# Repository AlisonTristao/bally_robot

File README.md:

# 🤖 Bally Robot

Projeto do robô seguidor de linha bally

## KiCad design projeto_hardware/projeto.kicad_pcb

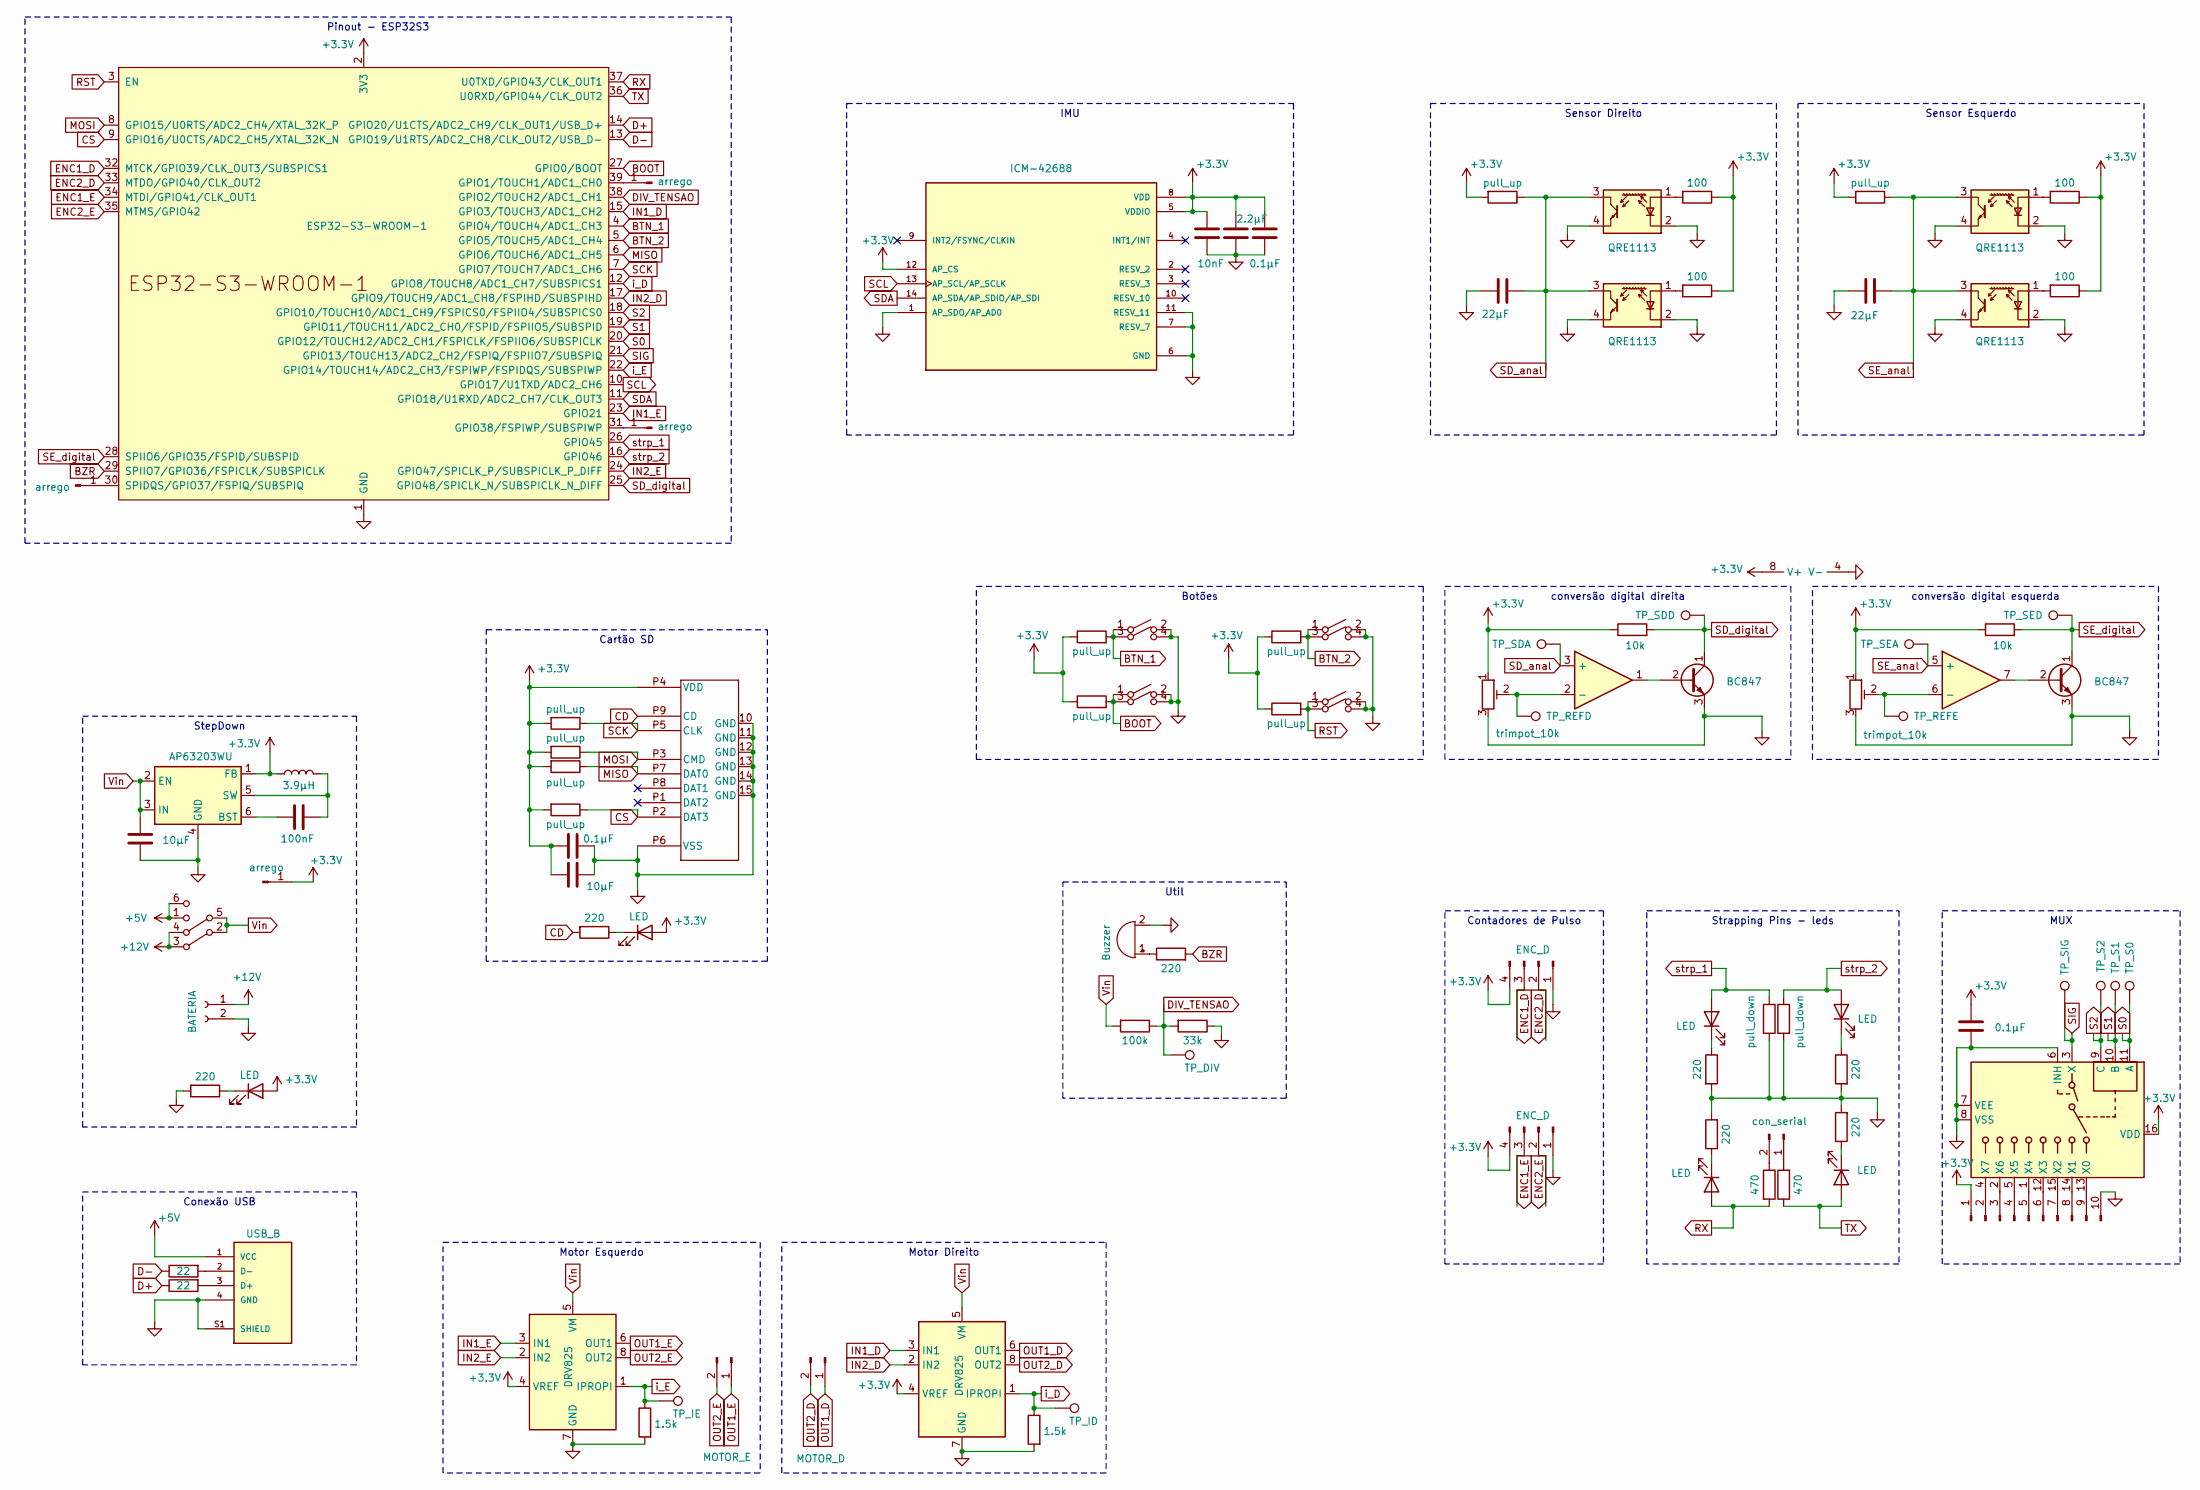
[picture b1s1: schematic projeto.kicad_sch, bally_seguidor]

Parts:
BZ1: Buzzer; MagneticBuzzer_CUI_CMT-8504-100-SMT_3d
C1, C5: 22µF; C_0805_2012Metric_Pad1.18x1.45mm_HandSolder
C2: 100nF; C_0805_2012Metric_Pad1.18x1.45mm_HandSolder
C3: 2.2µF; C_0805_2012Metric_Pad1.18x1.45mm_HandSolder
C4, C10: 10µF; C_0805_2012Metric_Pad1.18x1.45mm_HandSolder
C6, C8, C9: 0.1µF; C_0805_2012Metric_Pad1.18x1.45mm_HandSolder
C7: 10nF; C_0805_2012Metric_Pad1.18x1.45mm_HandSolder
Conn_01x02_Pin1: MOTOR_E; PinSocket_1x02_P2.54mm_Vertical
Conn_01x02_Pin2: con_serial; PinHeader_1x02_P2.54mm_Vertical
Conn_01x02_Pin3: MOTOR_D; PinSocket_1x02_P2.54mm_Vertical
Conn_01x04_Pin1, Conn_01x04_Pin2: ENC_D; PinSocket_1x04_P2.54mm_Vertical
D1, D2, D3, D4, D5, D6: LED; R_0805_2012Metric_Pad1.20x1.40mm_HandSolder
J1, J2, J4, J5: arrego; PinHeader_1x01_P2.54mm_Vertical
J3: Conn_01x10_Pin; PinHeader_1x10_P2.54mm_Vertical
J6: MEM2075-00-140-01-A; MEM2075-00-140-01-A_GCT
L1: 3.9µH; L_APV_APH1040
Q1, Q2: BC847; SOT-23
R1, R8, R9, R16: 100; R_0805_2012Metric_Pad1.20x1.40mm_HandSolder
R2, R10, R14, R18, R19, R20, R26, R27, R28, R29: pull_up; R_0805_2012Metric_Pad1.20x1.40mm_HandSolder
R3, R13: 10k; R_0805_2012Metric_Pad1.20x1.40mm_HandSolder
R4, R6, R12, R17, R21, R30, R31: 220; R_0805_2012Metric_Pad1.20x1.40mm_HandSolder
R5, R7: pull_down; R_0805_2012Metric_Pad1.20x1.40mm_HandSolder
R11, R15: 1.5k; R_0805_2012Metric_Pad1.20x1.40mm_HandSolder
R22: 100k; R_0805_2012Metric_Pad1.20x1.40mm_HandSolder
R23, R24: 470; R_0805_2012Metric_Pad1.20x1.40mm_HandSolder
R25: 33k; R_0805_2012Metric_Pad1.20x1.40mm_HandSolder
R32, R33: 22; R_0805_2012Metric_Pad1.20x1.40mm_HandSolder
RV1, RV2: trimpot_10k; Potentiometer_Bourns_3314G_Vertical
SW1: BOOT; SW_SMD_6mm
SW2: BTN2; SW_SMD_6mm
SW3: RST; SW_SMD_6mm
SW5: BTN1; SW_SMD_6mm
SW6: SW_DPDT_x2; SW_CK_JS202011CQN_DPDT_Straight
TP10: TP_IE; TestPoint_Pad_D1.0mm
TP11: TP_ID; TestPoint_Pad_D1.0mm
TP16: TP_DIV; TestPoint_Pad_D1.0mm
TP17: TP_S0; TestPoint_Pad_D1.0mm
TP18: TP_S1; TestPoint_Pad_D1.0mm
TP19: TP_S2; TestPoint_Pad_D1.0mm
TP21: TP_SIG; TestPoint_Pad_D1.0mm
TP25: TP_SED; TestPoint_Pad_D1.0mm
TP26: TP_SDD; TestPoint_Pad_D1.0mm
TP27: TP_SDA; TestPoint_Pad_D1.0mm
TP28: TP_SEA; TestPoint_Pad_D1.0mm
TP29: TP_REFD; TestPoint_Pad_D1.0mm
TP30: TP_REFE; TestPoint_Pad_D1.0mm
U1: ESP32-S3-WROOM-1
U2, U3, U7, U8: QRE1113; OnSemi_CASE100CY
U4: ICM-42688; PARTREV 1.2
U5, U6: DRV825
U9: LM358
U10: AP63203WU; TSOT-23-6
U11: CD4051B; MUX
USB-B-S-X-X-TH1: USB_B; USB-B; PARTREV Q
con1: BATERIA; Samtec_HPM-02-01-x-S_Straight_1x02_Pitch5.08mm

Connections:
+3.3V: C3.1, C6.1, C7.1, C8.1, C9.1, C10.1, Conn_01x04_Pin1.4, Conn_01x04_Pin2.4, D1.2 (A), D6.2 (A), J1.1, J3.1, J6.P4 (VDD), L1.2, R1.1, R2.2, R3.1, R8.1, R9.1, R10.1, R13.1, R14.2, R16.1, R18.1, R19.1, R20.1, R26.2, R27.2, R28.2, R29.2, RV1.1, RV2.1, U1.2 (3V3), U4.5 (VDDIO), U4.8 (VDD), U4.12 (AP_CS), U5.4 (VREF), U6.4 (VREF), U9.8 (V+), U10.1 (FB), U11.16 (VDD)
+5V: SW6.1 (C), SW6.6 (C), USB-B-S-X-X-TH1.1 (VCC)
+12V: SW6.3 (A), SW6.4 (A), con1.1
BOOT: R19.2, SW1.1 (A), SW1.3 (A), U1.27 (GPIO0/BOOT)
BTN_1: R10.2, SW5.1 (A), SW5.3 (A), U1.4 (GPIO4/TOUCH4/ADC1_CH3)
BTN_2: R18.2, SW2.1 (A), SW2.3 (A), U1.5 (GPIO5/TOUCH5/ADC1_CH4)
BZR: R21.2, U1.29 (SPIIO7/GPIO36/FSPICLK/SUBSPICLK)
CD: J6.P9 (CD), R30.2
CS: J6.P2 (DAT3), R28.1, U1.9 (GPIO16/U0CTS/ADC2_CH5/XTAL_32K_N)
D+: R33.1, U1.14 (GPIO20/U1CTS/ADC2_CH9/CLK_OUT1/USB_D+)
D-: R32.1, U1.13 (GPIO19/U1RTS/ADC2_CH8/CLK_OUT2/USB_D-)
DIV_TENSAO: R22.1, R25.2, TP16.1, U1.38 (GPIO2/TOUCH2/ADC1_CH1)
ENC1_D: Conn_01x04_Pin2.3, U1.32 (MTCK/GPIO39/CLK_OUT3/SUBSPICS1)
ENC1_E: Conn_01x04_Pin1.3, U1.34 (MTDI/GPIO41/CLK_OUT1)
ENC2_D: Conn_01x04_Pin2.2, U1.33 (MTDO/GPIO40/CLK_OUT2)
ENC2_E: Conn_01x04_Pin1.2, U1.35 (MTMS/GPIO42)
GND: BZ1.2 (+), C1.1, C3.2, C4.1, C5.1, C6.2, C7.2, C8.2, C9.2, C10.2, Conn_01x04_Pin1.1, Conn_01x04_Pin2.1, J3.10, J6.10 (GND), J6.11 (GND), J6.12 (GND), J6.13 (GND), J6.14 (GND), J6.15 (GND), J6.P6 (VSS), Q1.3 (E), Q2.3 (E), R4.2, R5.2, R6.2, R7.2, R11.2, R12.2, R15.2, R17.2, R25.1, R31.2, RV1.3, RV2.3, SW1.2 (B), SW1.4 (B), SW2.2 (B), SW2.4 (B), SW3.2 (B), SW3.4 (B), SW5.2 (B), SW5.4 (B), U1.1 (GND), U1.40 (GND), U1.41 (GND), U2.2 (K), U2.4, U3.2 (K), U3.4, U4.1 (AP_SDO/AP_AD0), U4.6 (GND), U4.7 (RESV_7), U4.11 (RESV_11), U5.7 (GND), U5.9 (GND), U6.7 (GND), U6.9 (GND), U7.2 (K), U7.4, U8.2 (K), U8.4, U9.4 (V-), U10.4 (GND), U11.6 (INH), U11.7 (VEE), U11.8 (VSS), USB-B-S-X-X-TH1.4 (GND), USB-B-S-X-X-TH1.S1 (SHIELD), USB-B-S-X-X-TH1.S2 (SHIELD), con1.2
IN1_D: U1.15 (GPIO3/TOUCH3/ADC1_CH2), U6.3 (IN1)
IN1_E: U1.23 (GPIO21), U5.3 (IN1)
IN2_D: U1.17 (GPIO9/TOUCH9/ADC1_CH8/FSPIHD/SUBSPIHD), U6.2 (IN2)
IN2_E: U1.24 (GPIO47/SPICLK_P/SUBSPICLK_P_DIFF), U5.2 (IN2)
MISO: J6.P7 (DAT0), R26.1, U1.6 (GPIO6/TOUCH6/ADC1_CH5)
MOSI: J6.P3 (CMD), R27.1, U1.8 (GPIO15/U0RTS/ADC2_CH4/XTAL_32K_P)
unnamed: BZ1.1 (-), R21.1
unnamed: Conn_01x02_Pin2.1, R23.2
unnamed: Conn_01x02_Pin2.2, R24.1
unnamed: D1.1 (K), R31.1
unnamed: D2.1 (K), R4.1
unnamed: D3.1 (K), R6.1
unnamed: D4.1 (K), R12.1
unnamed: D5.1 (K), R17.1
unnamed: D6.1 (K), R30.1
unnamed: J2.1, U1.39 (GPIO1/TOUCH1/ADC1_CH0)
unnamed: J3.2, U11.4 (X7)
unnamed: J3.3, U11.2 (X6)
unnamed: J3.4, U11.5 (X5)
unnamed: J3.5, U11.1 (X4)
unnamed: J3.6, U11.12 (X3)
unnamed: J3.7, U11.15 (X2)
unnamed: J3.8, U11.14 (X1)
unnamed: J3.9, U11.13 (X0)
unnamed: J4.1, U1.31 (GPIO38/FSPIWP/SUBSPIWP)
unnamed: J5.1, U1.30 (SPIDQS/GPIO37/FSPIQ/SUBSPIQ)
unnamed: Q1.2 (B), U9.1
unnamed: Q2.2 (B), U9.7
unnamed: R8.2, U2.1 (A)
unnamed: R9.2, U3.1 (A)
unnamed: R16.2, U7.1 (A)
unnamed: R1.2, U8.1 (A)
unnamed: RV1.2, TP29.1, U9.2 (-)
unnamed: RV2.2, TP30.1, U9.6 (-)
unnamed: C2.1, U10.6 (BST)
unnamed: C2.2, L1.1, U10.5 (SW)
unnamed: R33.2, USB-B-S-X-X-TH1.3 (D+)
unnamed: R32.2, USB-B-S-X-X-TH1.2 (D-)
OUT1_D: Conn_01x02_Pin3.1, U6.6 (OUT1)
OUT1_E: Conn_01x02_Pin1.1, U5.6 (OUT1)
OUT2_D: Conn_01x02_Pin3.2, U6.8 (OUT2)
OUT2_E: Conn_01x02_Pin1.2, U5.8 (OUT2)
RST: R20.2, SW3.1 (A), SW3.3 (A), U1.3 (EN)
RX: D5.2 (A), R24.2, U1.37 (U0TXD/GPIO43/CLK_OUT1)
S0: TP17.1, U1.20 (GPIO12/TOUCH12/ADC2_CH1/FSPICLK/FSPIIO6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), U11.11 (A)
S1: TP18.1, U1.19 (GPIO11/TOUCH11/ADC2_CH0/FSPID/FSPIIO5/S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), U11.10 (B)
S2: TP19.1, U1.18 (GPIO10/TOUCH10/ADC1_CH9/FSPICS0/FSPIIO4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), U11.9 (C)
SCK: J6.P5 (CLK), R29.1, U1.7 (GPIO7/TOUCH7/ADC1_CH6)
SCL: U1.10 (GPIO17/U1TXD/ADC2_CH6), U4.13 (AP_SCL/AP_SCLK)
SDA: U1.11 (GPIO18/U1RXD/ADC2_CH7/CLK_OUT3), U4.14 (AP_SDA/AP_SDIO/AP_SDI)
SD_anal: C5.2, R14.1, TP27.1, U7.3, U8.3, U9.3 (+)
SD_digital: Q1.1 (C), R13.2, TP26.1, U1.25 (GPIO48/SPICLK_N/SUBSPICLK_N_DIFF)
SE_anal: C1.2, R2.1, TP28.1, U2.3, U3.3, U9.5 (+)
SE_digital: Q2.1 (C), R3.2, TP25.1, U1.28 (SPIIO6/GPIO35/FSPID/SUBSPID)
SIG: TP21.1, U1.21 (GPIO13/TOUCH13/ADC2_CH2/FSPIQ/FSPIIO7/S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), U11.3 (X)
TX: D4.2 (A), R23.1, U1.36 (U0RXD/GPIO44/CLK_OUT2)
Vin: C4.2, R22.2, SW6.2 (B), SW6.5 (B), U5.5 (VM), U6.5 (VM), U10.2 (EN), U10.3 (IN)
i_D: R15.1, TP11.1, U1.12 (GPIO8/TOUCH8/ADC1_CH7/SUBSPICS1), U6.1 (IPROPI)
i_E: R11.1, TP10.1, U1.22 (GPIO14/TOUCH14/ADC2_CH3/FSPIWP/FSPIDQS/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), U5.1 (IPROPI)
strp_1: D2.2 (A), R5.1, U1.26 (GPIO45)
strp_2: D3.2 (A), R7.1, U1.16 (GPIO46)

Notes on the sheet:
MUX
IMU
Cartão SD
Motor Direito
Util
StepDown
conversão digital direita
Motor Esquerdo
Conexão USB
Contadores de Pulso
Sensor Direito
conversão digital esquerda
Pinout - ESP32S3
Sensor Esquerdo
Strapping Pins - leds
Botões

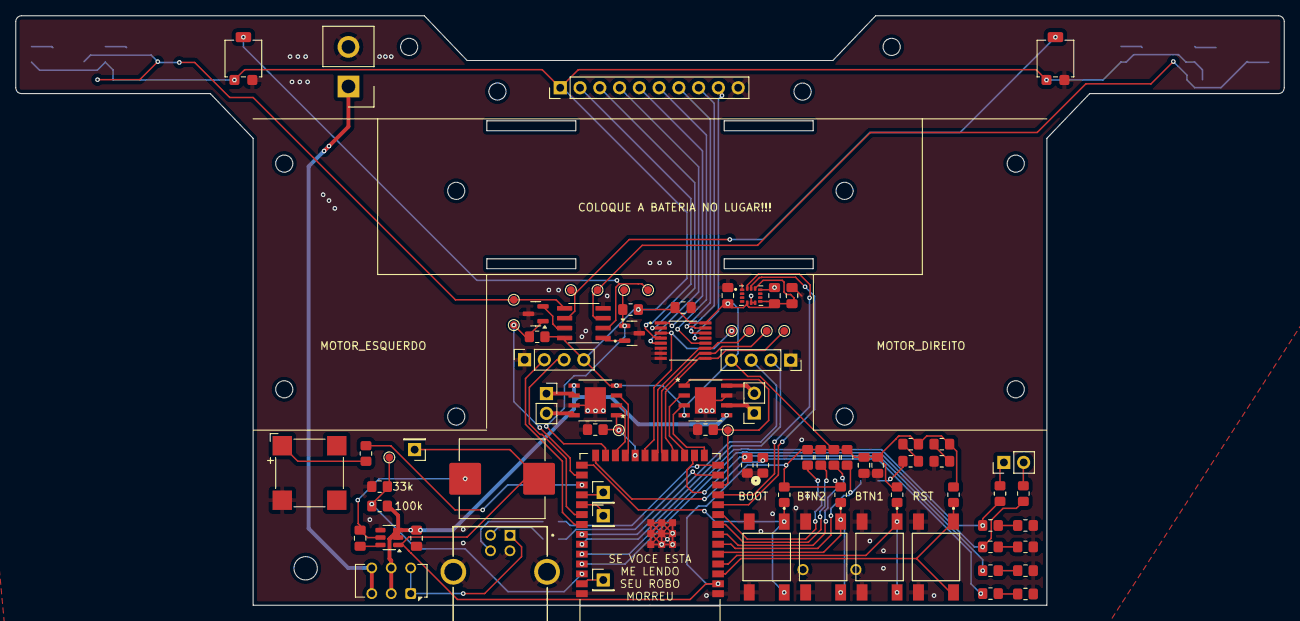
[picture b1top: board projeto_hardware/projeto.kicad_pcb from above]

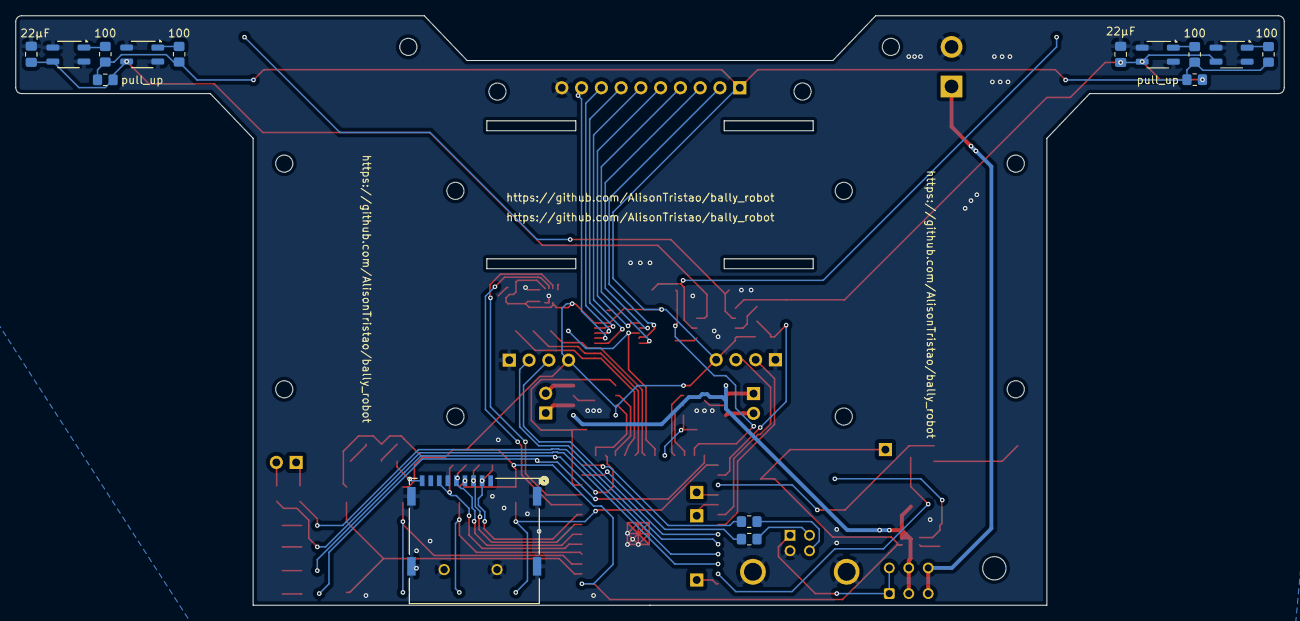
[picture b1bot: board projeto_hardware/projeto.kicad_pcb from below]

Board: 2 copper layers, 163.0 x 75.8 mm, 97 parts (15 on the bottom side), 78 nets.

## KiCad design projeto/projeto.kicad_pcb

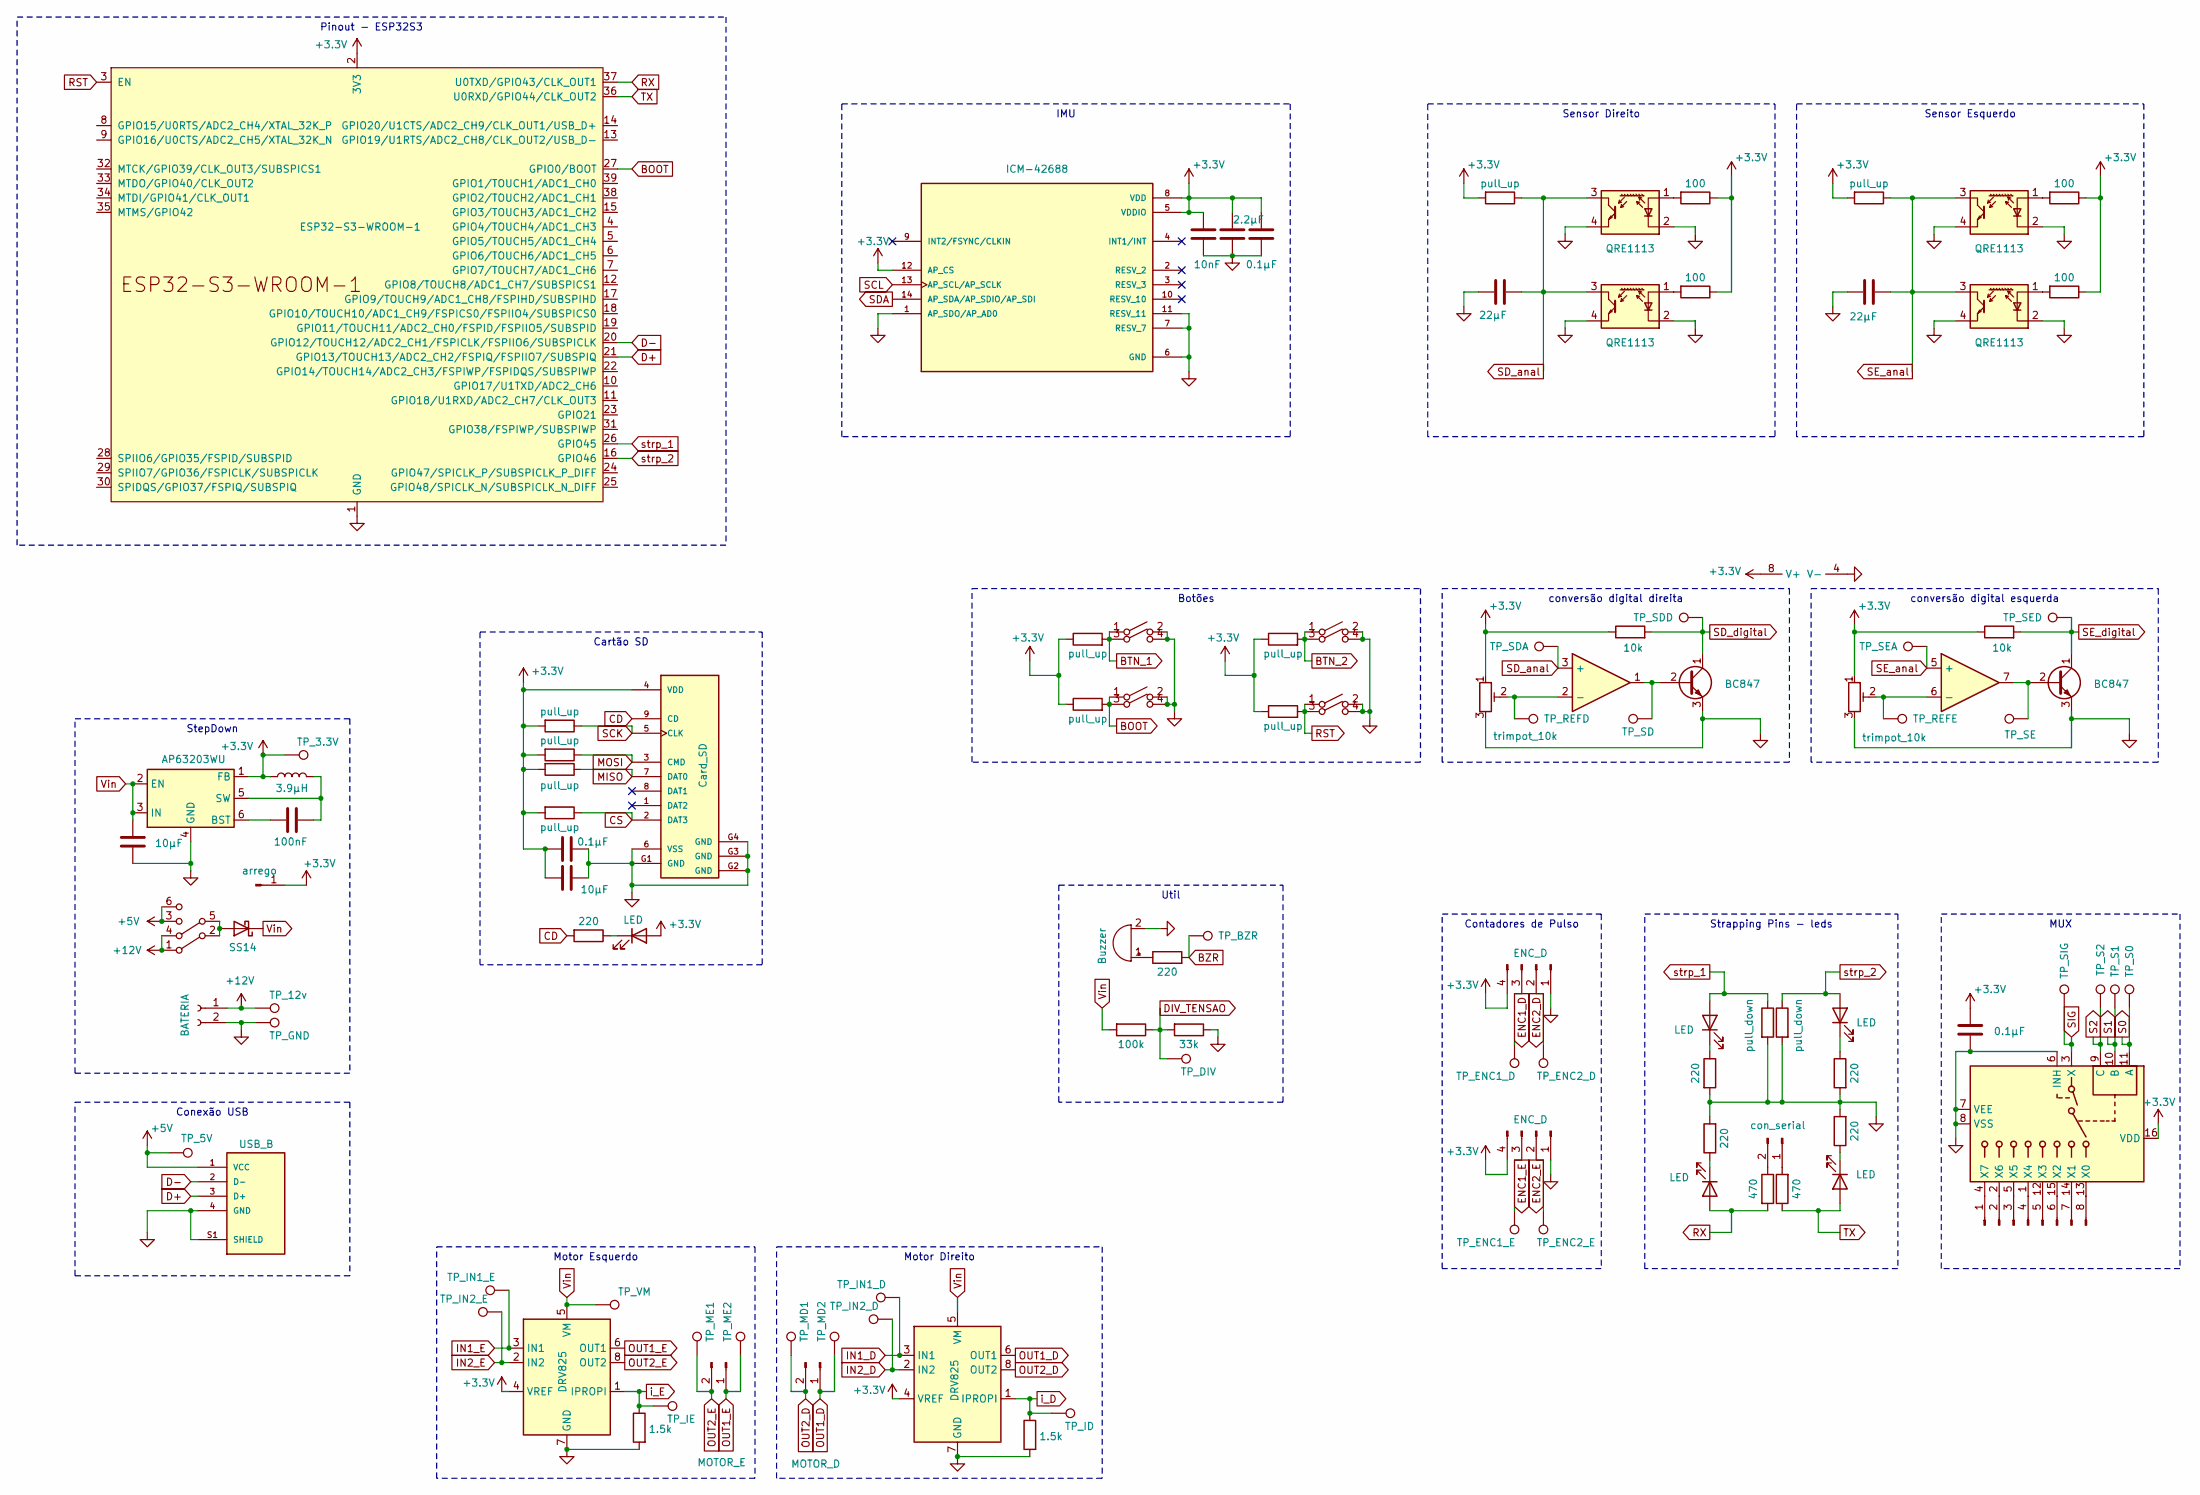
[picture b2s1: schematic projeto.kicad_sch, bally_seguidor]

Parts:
BZ1: Buzzer; Buzzer_12x9.5RM7.6
C1, C5: 22µF; C_0805_2012Metric_Pad1.18x1.45mm_HandSolder
C2: 100nF; C_0805_2012Metric_Pad1.18x1.45mm_HandSolder
C3: 2.2µF; C_0805_2012Metric_Pad1.18x1.45mm_HandSolder
C4, C10: 10µF; C_0805_2012Metric_Pad1.18x1.45mm_HandSolder
C6, C8, C9: 0.1µF; C_0805_2012Metric_Pad1.18x1.45mm_HandSolder
C7: 10nF; C_0805_2012Metric_Pad1.18x1.45mm_HandSolder
Conn_01x02_Pin1: MOTOR_E; PinSocket_1x02_P2.54mm_Vertical
Conn_01x02_Pin2: con_serial; PinHeader_1x02_P2.54mm_Vertical
Conn_01x02_Pin3: MOTOR_D; PinSocket_1x02_P2.54mm_Vertical
Conn_01x04_Pin1, Conn_01x04_Pin2: ENC_D; PinSocket_1x04_P2.54mm_Vertical
D1: SS14; D_SMA
D2, D3, D4, D5, D6: LED; R_0805_2012Metric_Pad1.20x1.40mm_HandSolder
J1: arrego; PinHeader_1x01_P2.54mm_Vertical
J2: Conn_01x08_Pin; PinHeader_1x08_P2.54mm_Vertical
L1: 3.9µH; L_APV_APH1040
P1: Card_SD; Micro_SD_card
Q1, Q2: BC847; SOT-23
R1, R8, R9, R16: 100; R_0805_2012Metric_Pad1.20x1.40mm_HandSolder
R2, R10, R14, R18, R19, R20, R26, R27, R28, R29: pull_up; R_0805_2012Metric_Pad1.20x1.40mm_HandSolder
R3, R13: 10k; R_0805_2012Metric_Pad1.20x1.40mm_HandSolder
R4, R6, R12, R17, R21, R30: 220; R_0805_2012Metric_Pad1.20x1.40mm_HandSolder
R5, R7: pull_down; R_0805_2012Metric_Pad1.20x1.40mm_HandSolder
R11, R15: 1.5k; R_0805_2012Metric_Pad1.20x1.40mm_HandSolder
R22: 100k; R_1206_3216Metric
R23, R24: 470; R_0805_2012Metric_Pad1.20x1.40mm_HandSolder
R25: 33k; R_1206_3216Metric
RV1, RV2: trimpot_10k; Potentiometer_Bourns_3314G_Vertical
SW1, SW2, SW3, SW5: SW_DPST_x2; SW_SMD_6mm
SW6: SW_DPDT_x2; SW_CK_JS202011CQN_DPDT_Straight
TP1: TP_12v; TestPoint_Pad_D1.0mm
TP2: TP_GND; TestPoint_Pad_D1.0mm
TP3: TP_3.3V; TestPoint_Pad_D1.0mm
TP4: TP_5V; TestPoint_Pad_D1.0mm
TP5: TP_ME1; TestPoint_Pad_D1.0mm
TP6: TP_ME2; TestPoint_Pad_D1.0mm
TP7: TP_MD1; TestPoint_Pad_D1.0mm
TP8: TP_MD2; TestPoint_Pad_D1.0mm
TP9: TP_VM; TestPoint_Pad_D1.0mm
TP10: TP_IE; TestPoint_Pad_D1.0mm
TP11: TP_ID; TestPoint_Pad_D1.0mm
TP12: TP_IN1_E; TestPoint_Pad_D1.0mm
TP13: TP_IN2_E; TestPoint_Pad_D1.0mm
TP14: TP_IN2_D; TestPoint_Pad_D1.0mm
TP15: TP_IN1_D; TestPoint_Pad_D1.0mm
TP16: TP_DIV; TestPoint_Pad_D1.0mm
TP17: TP_S0; TestPoint_Pad_D1.0mm
TP18: TP_S1; TestPoint_Pad_D1.0mm
TP19: TP_S2; TestPoint_Pad_D1.0mm
TP21: TP_SIG; TestPoint_Pad_D1.0mm
TP22: TP_BZR; TestPoint_Pad_D1.0mm
TP23: TP_SE; TestPoint_Pad_D1.0mm
TP24: TP_SD; TestPoint_Pad_D1.0mm
TP25: TP_SED; TestPoint_Pad_D1.0mm
TP26: TP_SDD; TestPoint_Pad_D1.0mm
TP27: TP_SDA; TestPoint_Pad_D1.0mm
TP28: TP_SEA; TestPoint_Pad_D1.0mm
TP29: TP_REFD; TestPoint_Pad_D1.0mm
TP30: TP_REFE; TestPoint_Pad_D1.0mm
TP31: TP_ENC1_E; TestPoint_Pad_D1.0mm
TP32: TP_ENC2_E; TestPoint_Pad_D1.0mm
TP33: TP_ENC1_D; TestPoint_Pad_D1.0mm
TP34: TP_ENC2_D; TestPoint_Pad_D1.0mm
U1: ESP32-S3-WROOM-1
U2, U3, U7, U8: QRE1113; OnSemi_CASE100CY
U4: ICM-42688; PARTREV 1.2
U5, U6: DRV825
U9: LM358
U10: AP63203WU; TSOT-23-6
U11: CD4051B; MUX
USB-B-S-X-X-TH1: USB_B; USB-B; PARTREV Q
con1: BATERIA; Samtec_HPM-02-01-x-S_Straight_1x02_Pitch5.08mm

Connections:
+3.3V: C3.1, C6.1, C7.1, C8.1, C9.1, C10.1, Conn_01x04_Pin1.4, Conn_01x04_Pin2.4, D6.2 (A), J1.1, L1.2, P1.4 (VDD), R1.1, R2.2, R3.1, R8.1, R9.1, R10.1, R13.1, R14.2, R16.1, R18.1, R19.1, R20.1, R26.2, R27.2, R28.2, R29.2, RV1.1, RV2.1, TP3.1, U1.2 (3V3), U4.5 (VDDIO), U4.8 (VDD), U4.12 (AP_CS), U5.4 (VREF), U6.4 (VREF), U9.8 (V+), U10.1 (FB), U11.16 (VDD)
+5V: SW6.3 (C), SW6.6 (C), TP4.1, USB-B-S-X-X-TH1.1 (VCC)
+12V: SW6.1 (A), SW6.4 (A), TP1.1, con1.1
BOOT: R19.2, SW1.1 (A), SW1.3 (A), U1.27 (GPIO0/BOOT)
BTN_1: R10.2, SW5.1 (A), SW5.3 (A)
BTN_2: R18.2, SW2.1 (A), SW2.3 (A)
BZR: R21.2, TP22.1
CD: P1.9 (CD), R30.2
CS: P1.2 (DAT3), R28.1
D+: U1.21 (GPIO13/TOUCH13/ADC2_CH2/FSPIQ/FSPIIO7/S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), USB-B-S-X-X-TH1.3 (D+)
D-: U1.20 (GPIO12/TOUCH12/ADC2_CH1/FSPICLK/FSPIIO6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), USB-B-S-X-X-TH1.2 (D-)
DIV_TENSAO: R22.1, R25.2, TP16.1
ENC1_D: Conn_01x04_Pin2.3, TP33.1
ENC1_E: Conn_01x04_Pin1.3, TP31.1
ENC2_D: Conn_01x04_Pin2.2, TP34.1
ENC2_E: Conn_01x04_Pin1.2, TP32.1
GND: BZ1.2 (+), C1.1, C3.2, C4.1, C5.1, C6.2, C7.2, C8.2, C9.2, C10.2, Conn_01x04_Pin1.1, Conn_01x04_Pin2.1, P1.6 (VSS), P1.G1 (GND), P1.G2 (GND), P1.G3 (GND), P1.G4 (GND), Q1.3 (E), Q2.3 (E), R4.2, R5.2, R6.2, R7.2, R11.2, R12.2, R15.2, R17.2, R25.1, RV1.3, RV2.3, SW1.2 (B), SW1.4 (B), SW2.2 (B), SW2.4 (B), SW3.2 (B), SW3.4 (B), SW5.2 (B), SW5.4 (B), TP2.1, U1.1 (GND), U1.40 (GND), U1.41 (GND), U2.2 (K), U2.4, U3.2 (K), U3.4, U4.1 (AP_SDO/AP_AD0), U4.6 (GND), U4.7 (RESV_7), U4.11 (RESV_11), U5.7 (GND), U5.9 (GND), U6.7 (GND), U6.9 (GND), U7.2 (K), U7.4, U8.2 (K), U8.4, U9.4 (V-), U10.4 (GND), U11.6 (INH), U11.7 (VEE), U11.8 (VSS), USB-B-S-X-X-TH1.4 (GND), USB-B-S-X-X-TH1.S1 (SHIELD), USB-B-S-X-X-TH1.S2 (SHIELD), con1.2
IN1_D: TP15.1, U6.3 (IN1)
IN1_E: TP12.1, U5.3 (IN1)
IN2_D: TP14.1, U6.2 (IN2)
IN2_E: TP13.1, U5.2 (IN2)
MISO: P1.7 (DAT0), R26.1
MOSI: P1.3 (CMD), R27.1
unnamed: BZ1.1 (-), R21.1
unnamed: Conn_01x02_Pin2.1, R23.2
unnamed: Conn_01x02_Pin2.2, R24.1
unnamed: D1.2 (A), SW6.2 (B), SW6.5 (B)
unnamed: D2.1 (K), R4.1
unnamed: D3.1 (K), R6.1
unnamed: D4.1 (K), R12.1
unnamed: D5.1 (K), R17.1
unnamed: D6.1 (K), R30.1
unnamed: J2.1, U11.4 (X7)
unnamed: J2.2, U11.2 (X6)
unnamed: J2.3, U11.5 (X5)
unnamed: J2.4, U11.1 (X4)
unnamed: J2.5, U11.12 (X3)
unnamed: J2.6, U11.15 (X2)
unnamed: J2.7, U11.14 (X1)
unnamed: J2.8, U11.13 (X0)
unnamed: Q1.2 (B), TP24.1, U9.1
unnamed: Q2.2 (B), TP23.1, U9.7
unnamed: R8.2, U2.1 (A)
unnamed: R9.2, U3.1 (A)
unnamed: R16.2, U7.1 (A)
unnamed: R1.2, U8.1 (A)
unnamed: RV1.2, TP29.1, U9.2 (-)
unnamed: RV2.2, TP30.1, U9.6 (-)
unnamed: C2.1, U10.6 (BST)
unnamed: C2.2, L1.1, U10.5 (SW)
OUT1_D: Conn_01x02_Pin3.1, TP8.1, U6.6 (OUT1)
OUT1_E: Conn_01x02_Pin1.1, TP6.1, U5.6 (OUT1)
OUT2_D: Conn_01x02_Pin3.2, TP7.1, U6.8 (OUT2)
OUT2_E: Conn_01x02_Pin1.2, TP5.1, U5.8 (OUT2)
RST: R20.2, SW3.1 (A), SW3.3 (A), U1.3 (EN)
RX: D5.2 (A), R24.2, U1.37 (U0TXD/GPIO43/CLK_OUT1)
S0: TP17.1, U11.11 (A)
S1: TP18.1, U11.10 (B)
S2: TP19.1, U11.9 (C)
SCK: P1.5 (CLK), R29.1
SCL: U4.13 (AP_SCL/AP_SCLK)
SDA: U4.14 (AP_SDA/AP_SDIO/AP_SDI)
SD_anal: C5.2, R14.1, TP27.1, U7.3, U8.3, U9.3 (+)
SD_digital: Q1.1 (C), R13.2, TP26.1
SE_anal: C1.2, R2.1, TP28.1, U2.3, U3.3, U9.5 (+)
SE_digital: Q2.1 (C), R3.2, TP25.1
SIG: TP21.1, U11.3 (X)
TX: D4.2 (A), R23.1, U1.36 (U0RXD/GPIO44/CLK_OUT2)
Vin: C4.2, D1.1 (K), R22.2, TP9.1, U5.5 (VM), U6.5 (VM), U10.2 (EN), U10.3 (IN)
i_D: R15.1, TP11.1, U6.1 (IPROPI)
i_E: R11.1, TP10.1, U5.1 (IPROPI)
strp_1: D2.2 (A), R5.1, U1.26 (GPIO45)
strp_2: D3.2 (A), R7.1, U1.16 (GPIO46)

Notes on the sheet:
MUX
IMU
Cartão SD
Motor Direito
Util
StepDown
conversão digital direita
Motor Esquerdo
Conexão USB
Contadores de Pulso
Sensor Direito
conversão digital esquerda
Pinout - ESP32S3
Sensor Esquerdo
Strapping Pins - leds
Botões

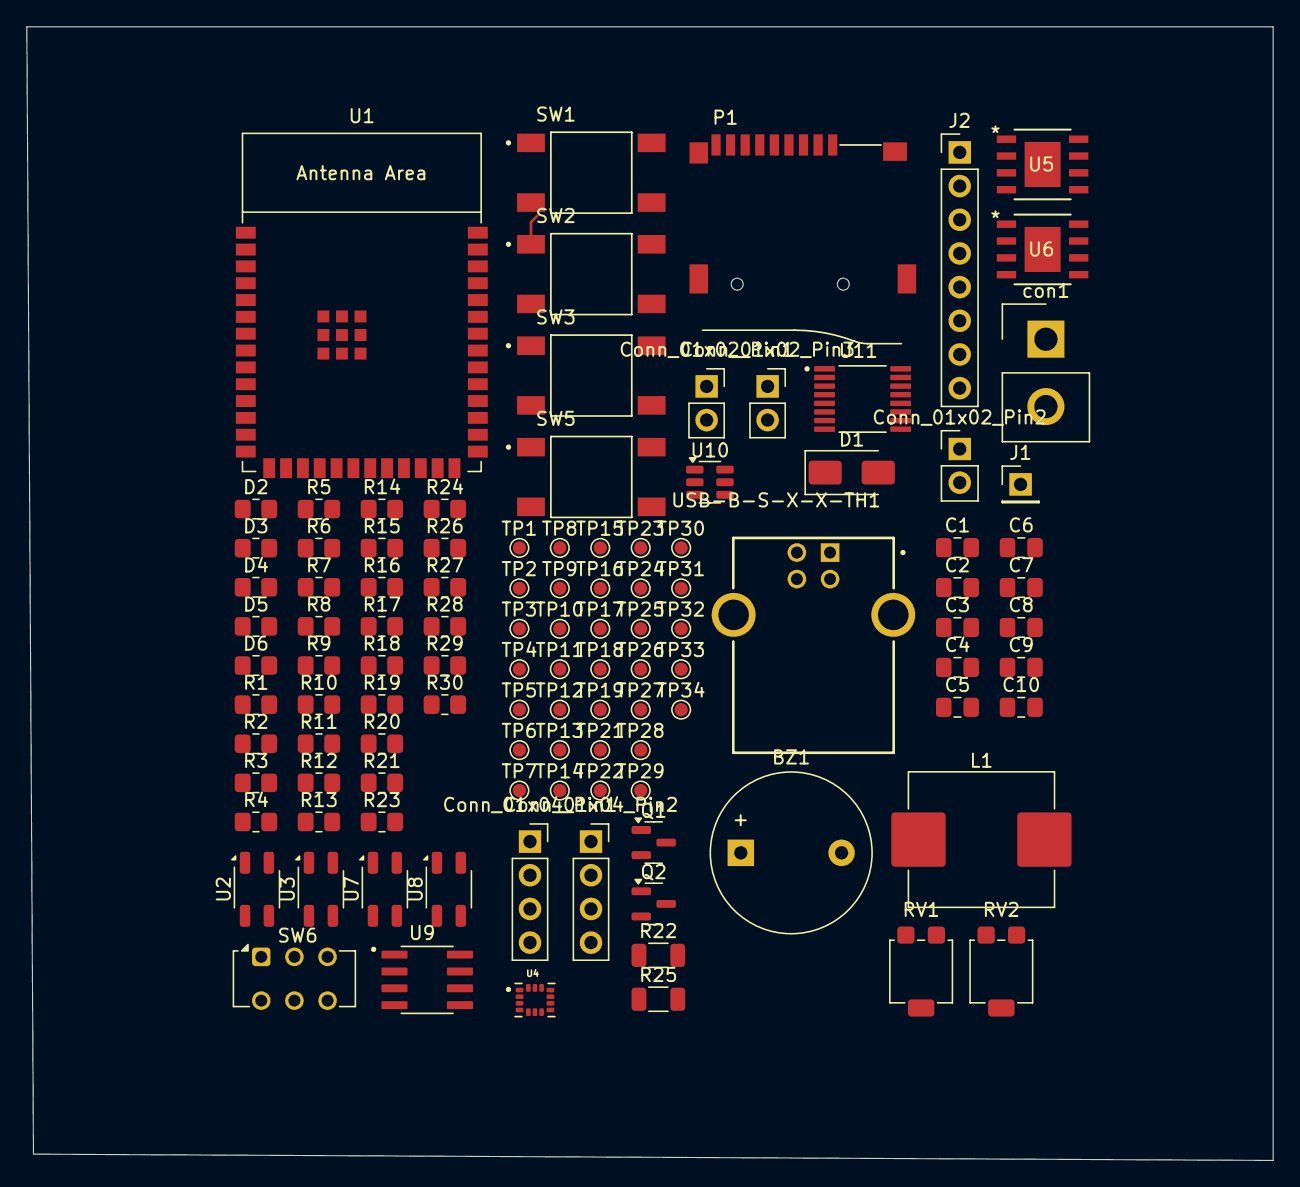
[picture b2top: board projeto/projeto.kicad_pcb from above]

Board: 2 copper layers, 94.0 x 85.5 mm, 111 parts (0 on the bottom side), 71 nets.

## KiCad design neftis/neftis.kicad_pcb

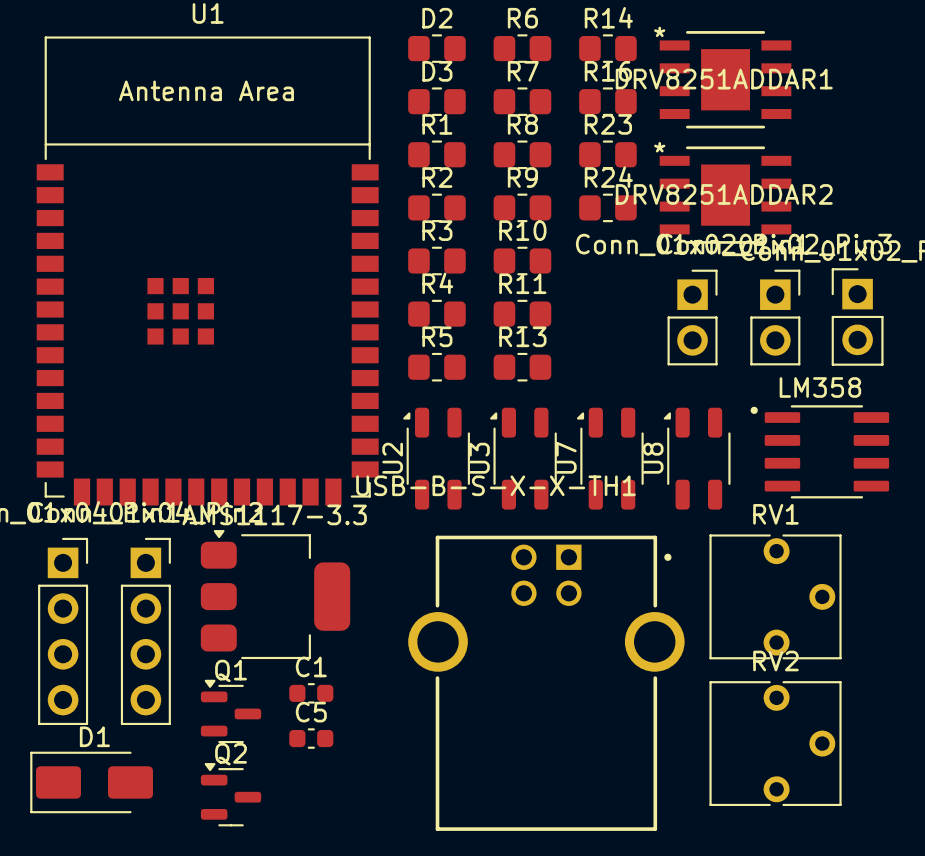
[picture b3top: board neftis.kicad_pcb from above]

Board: 2 copper layers, 40 parts (0 on the bottom side), 34 nets, no tracks yet.

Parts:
AMS1117-3.3: 5v_to_3.3v; SOT-223-3_TabPin2
C1, C5: 22; C_0603_1608Metric
Conn_01x02_Pin1, Conn_01x02_Pin3: MOTOR_D; PinSocket_1x02_P2.54mm_Vertical
Conn_01x02_Pin2: con_serial; PinHeader_1x02_P2.54mm_Vertical
Conn_01x04_Pin1, Conn_01x04_Pin2: ENC_D; PinSocket_1x04_P2.54mm_Vertical
D1: SS14; D_SMA
D2, D3: LED; R_0805_2012Metric_Pad1.20x1.40mm_HandSolder
DRV8251ADDAR1: Ponte_H_E; ponte_H
DRV8251ADDAR2: Ponte_H_D; ponte_H
LM358: Opamp_Dual; LM358
Q1, Q2: BC847; SOT-23
R1, R3, R8, R16: 100; R_0805_2012Metric_Pad1.20x1.40mm_HandSolder
R2, R14: pull_up; R_0805_2012Metric_Pad1.20x1.40mm_HandSolder
R4, R6: 220; R_0805_2012Metric_Pad1.20x1.40mm_HandSolder
R5, R7: pull_down; R_0805_2012Metric_Pad1.20x1.40mm_HandSolder
R9, R13: 10k; R_0805_2012Metric_Pad1.20x1.40mm_HandSolder
R10, R11: 1.5k; R_0805_2012Metric_Pad1.20x1.40mm_HandSolder
R23, R24: 470; R_0805_2012Metric_Pad1.20x1.40mm_HandSolder
RV1, RV2: trimpot_10k; Potentiometer_Vishay_T73YP_Vertical_com3d
U1: ESP32-S3-WROOM-1
U2, U3, U7, U8: QRE1113; OnSemi_CASE100CY
USB-B-S-X-X-TH1: USB_B; USB-B

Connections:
+3.3V: AMS1117-3.3.2 (VO), Conn_01x04_Pin1.4, Conn_01x04_Pin2.4, DRV8251ADDAR1.4 (VREF), DRV8251ADDAR2.4 (VREF)
+3V3: LM358.8 (V+), R1.1, R2.2, R3.1, R8.1, R9.1, R13.1, R14.2, R16.1, RV1.1, RV2.1, U1.2 (3V3)
+5V: AMS1117-3.3.3 (VI), D1.1 (K)
+12V: DRV8251ADDAR1.5 (VM), DRV8251ADDAR2.5 (VM)
D+: U1.21 (GPIO13/TOUCH13/ADC2_CH2/FSPIQ/FSPIIO7/S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), USB-B-S-X-X-TH1.3 (D+)
D-: U1.20 (GPIO12/TOUCH12/ADC2_CH1/FSPICLK/FSPIIO6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), USB-B-S-X-X-TH1.2 (D-)
GND: AMS1117-3.3.1 (GND), C1.1, C5.1, Conn_01x04_Pin1.1, Conn_01x04_Pin2.1, DRV8251ADDAR1.7 (GND), DRV8251ADDAR2.7 (GND), LM358.4 (V-), Q1.3 (E), Q2.3 (E), R4.2, R5.2, R6.2, R7.2, R10.2, R11.2, RV1.3, RV2.3, U1.1 (GND), U1.40 (GND), U1.41 (GND), U2.2 (K), U2.4, U3.2 (K), U3.4, U7.2 (K), U7.4, U8.2 (K), U8.4, USB-B-S-X-X-TH1.4 (GND), USB-B-S-X-X-TH1.S1 (SHIELD), USB-B-S-X-X-TH1.S2 (SHIELD)
unnamed: Conn_01x02_Pin2.1, R23.2
unnamed: Conn_01x02_Pin2.2, R24.1
unnamed: D1.2 (A), USB-B-S-X-X-TH1.1 (VCC)
unnamed: D2.1 (K), R4.1
unnamed: D3.1 (K), R6.1
unnamed: C1.2, LM358.3 (+), R2.1, U2.3, U3.3
unnamed: LM358.2 (-), RV2.2
unnamed: C5.2, LM358.5 (+), R14.1, U7.3, U8.3
unnamed: LM358.6 (-), RV1.2
unnamed: LM358.7, Q1.2 (B)
unnamed: LM358.1, Q2.2 (B)
unnamed: R3.2, U2.1 (A)
unnamed: R8.2, U3.1 (A)
unnamed: R16.2, U7.1 (A)
unnamed: R1.2, U8.1 (A)
OUT1_D: Conn_01x02_Pin3.1, DRV8251ADDAR2.6 (OUT1)
OUT1_E: Conn_01x02_Pin1.1, DRV8251ADDAR1.6 (OUT1)
OUT2_D: Conn_01x02_Pin3.2, DRV8251ADDAR2.8 (OUT2)
OUT2_E: Conn_01x02_Pin1.2, DRV8251ADDAR1.8 (OUT2)
RX: R23.1, U1.37 (U0TXD/GPIO43/CLK_OUT1)
SD_digital: Q1.1 (C), R13.2
SE_digital: Q2.1 (C), R9.2
TX: R24.2, U1.36 (U0RXD/GPIO44/CLK_OUT2)
i_D: DRV8251ADDAR2.1 (IPROPI), R10.1
i_E: DRV8251ADDAR1.1 (IPROPI), R11.1
strp_1: D2.2 (A), R5.1, U1.26 (GPIO45)
strp_2: D3.2 (A), R7.1, U1.16 (GPIO46)

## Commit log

2026-03-20 comecei os preparativos
2026-03-21 ponte H
2026-03-21 rename
2026-03-21 quase ponto
2026-03-23 quase tudo SMD vida boa
2026-03-25 falta só fazer as trilhas praticamente
2026-03-26 pronto - só revisar com calma
2026-03-26 parafuso m2 - div tensao 1/8W
2026-03-26 alimentacao 12v perto da bateria
2026-03-26 projeto step
2026-04-15 add resitor 22 ohms no USB
2026-04-24 mandei pros chineses fazerem

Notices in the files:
parts and their libraries:
Copyright: Copyright (C) 2023 Ultra Librarian. All rights reserved.
